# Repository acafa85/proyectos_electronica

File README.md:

# proyectos_electronica
Proyectos desarrollado: Inclinometro Digital con Sensor Digital

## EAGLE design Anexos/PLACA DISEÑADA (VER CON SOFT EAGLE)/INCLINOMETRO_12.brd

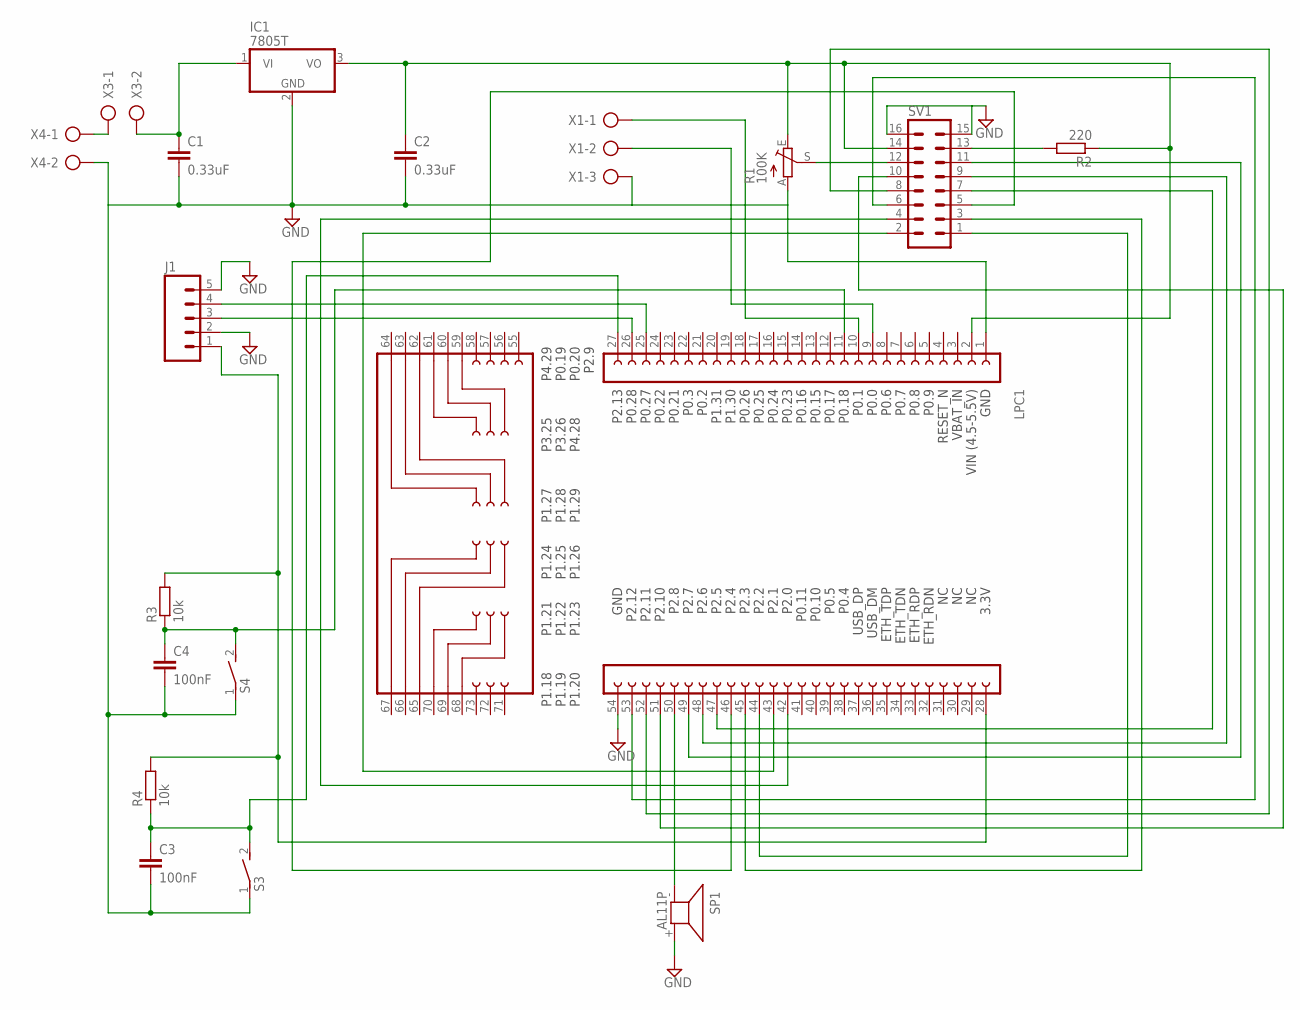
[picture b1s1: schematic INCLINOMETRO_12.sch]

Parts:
C1, C2: 0.33uF; C025-025X050
C3, C4: 100nF; C025-025X050
IC1: 7805T; TO220H
J1: M05PTH_LONGPADS; 1X05_LONGPADS
LPC1: LPCXPRESSO_LPC1769
R1: 100K; S64W
R2: 220; 0207/12
R3, R4: 10k; 0207/12
S3, S4: DS01E; DS-01
SP1: AL11P
SV1: ML16
X1: AK500/3
X3, X4: AK500/2

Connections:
GND: LPC1.54
unnamed: J1.3, LPC1.26
unnamed: LPC1.50, SP1.- (1)
unnamed: J1.4, LPC1.25
unnamed: C1.1, IC1.1 (VI), X3.2
unnamed: LPC1.52, SV1.8
unnamed: X3.1, X4.1
unnamed: R2.2, SV1.13
unnamed: LPC1.9, X1.2
unnamed: LPC1.10, X1.1
unnamed: C3.1, LPC1.27, R4.1, S3.2
unnamed: C2.1, IC1.3 (VO), LPC1.2, R1.E, R2.1, SV1.14
unnamed: R1.S, SV1.12
unnamed: J1.1, LPC1.28, R3.2, R4.2
unnamed: LPC1.43, SV1.2
unnamed: LPC1.51, SV1.10
unnamed: LPC1.53, SV1.6
unnamed: LPC1.42, SV1.4
unnamed: LPC1.49, SV1.11
unnamed: LPC1.48, SV1.9
unnamed: LPC1.45, SV1.3
unnamed: LPC1.47, SV1.7
unnamed: LPC1.46, SV1.5
unnamed: LPC1.44, SV1.1
unnamed: C4.1, LPC1.11, R3.1, S4.2
unnamed: C1.2, C2.2, C3.2, C4.2, IC1.2 (GND), J1.2, J1.5, LPC1.1, R1.A, S3.1, S4.1, SP1.+ (2), SV1.15, SV1.16, X1.3, X4.2

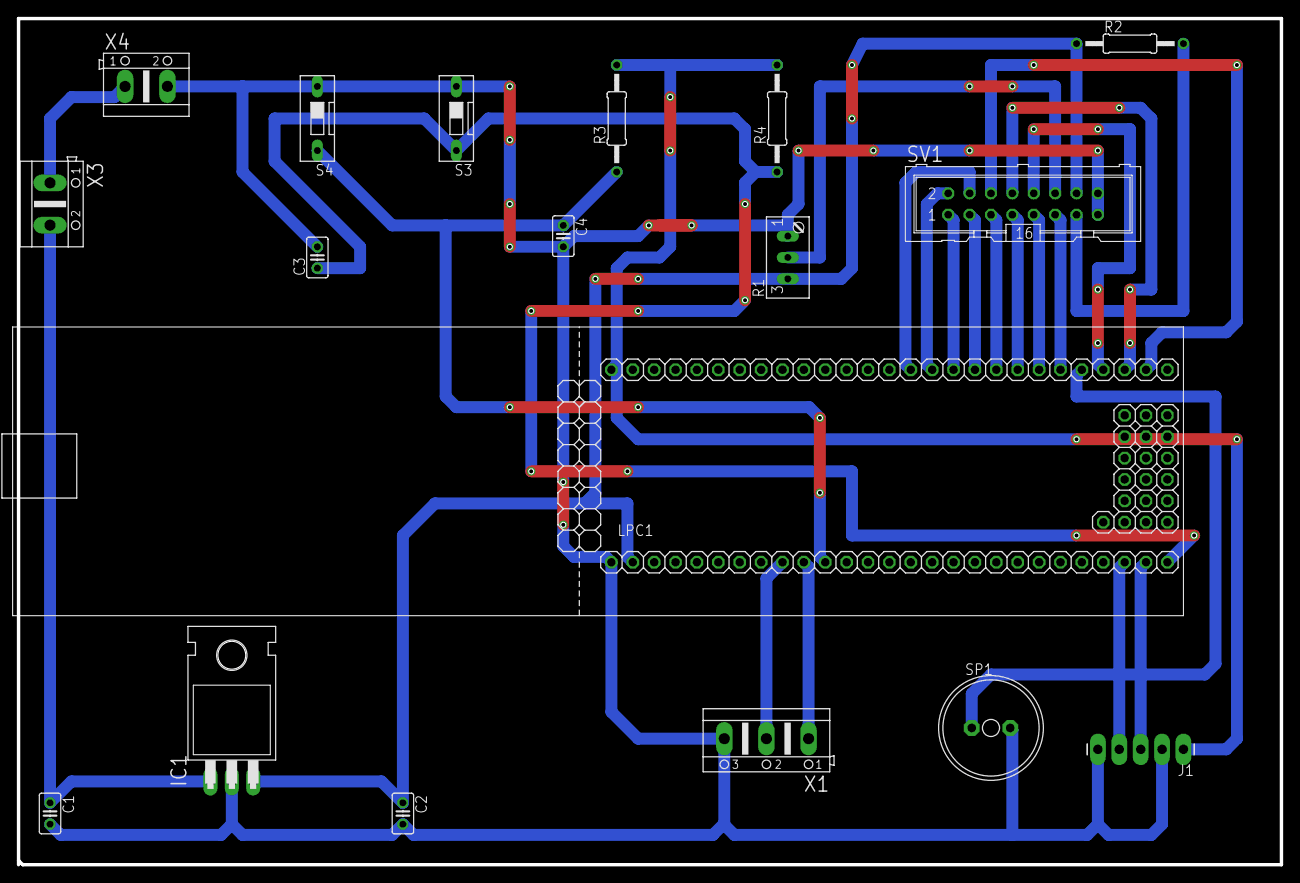
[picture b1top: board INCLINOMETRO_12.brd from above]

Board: 2 copper layers, 150.0 x 100.5 mm, 18 parts (0 on the bottom side), 25 nets.

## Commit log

2020-07-13 se sube trabajo desarrollado

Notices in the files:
parts and their libraries:
SparkFun-Connectors: Licensing: Creative Commons ShareAlike 4.0 International - https://creativecommons.org/licenses/by-sa/4.0
